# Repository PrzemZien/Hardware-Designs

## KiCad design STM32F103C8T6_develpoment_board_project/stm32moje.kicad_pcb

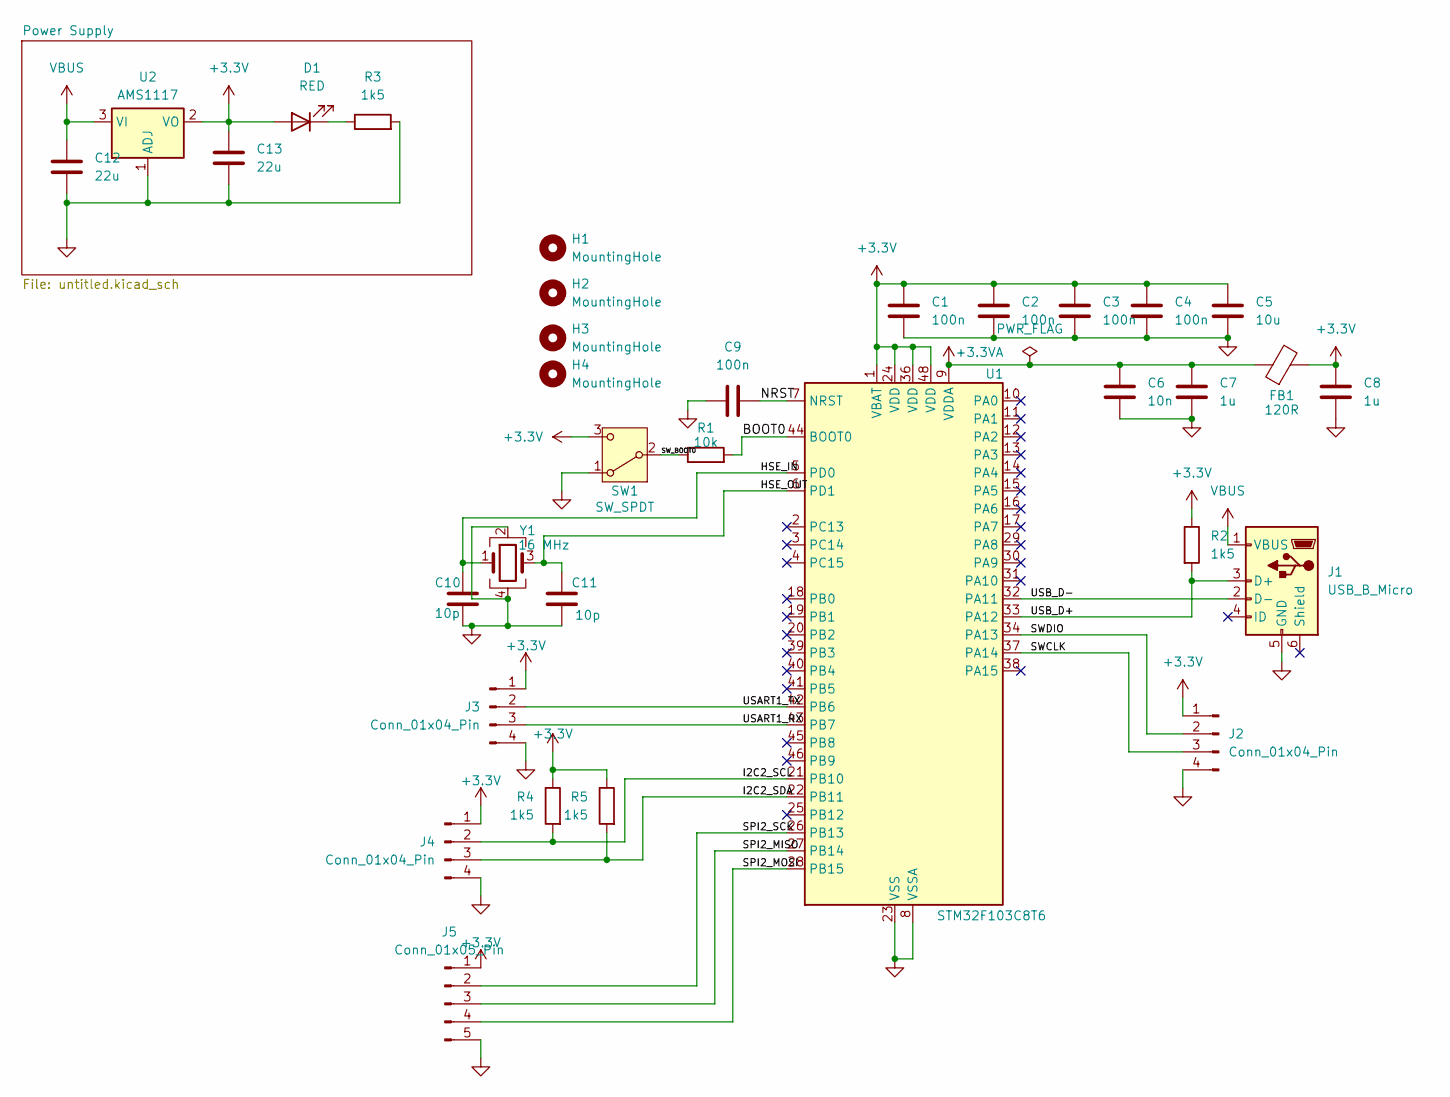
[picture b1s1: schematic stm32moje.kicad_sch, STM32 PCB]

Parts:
C1, C2, C3, C4, C9: 100n; C_0402_1005Metric
C5: 10u; C_0603_1608Metric
C6: 10n; C_0402_1005Metric
C7, C8: 1u; C_0402_1005Metric
C10, C11: 10p; C_0402_1005Metric
C12, C13: 22u; C_0805_2012Metric
D1: RED; LED_0603_1608Metric
FB1: 120R; L_0603_1608Metric
H1, H2, H3, H4: MountingHole; MountingHole_2.2mm_M2
J1: USB_B_Micro; USB_Micro-B_Wuerth_629105150521
J2, J3, J4: Conn_01x04_Pin; PinHeader_1x04_P2.54mm_Vertical
J5: Conn_01x05_Pin; JST_ZE_S05B-ZESK-2D_1x05_P1.50mm_Horizontal
R1: 10k; R_0402_1005Metric
R2, R3, R4, R5: 1k5; R_0402_1005Metric
SW1: SW_SPDT; SW_SPDT_PCM12
U1: STM32F103C8T6; LQFP-48_7x7mm_P0.5mm
U2: AMS1117; SOT-223-3_TabPin2
Y1: 16 MHz; Crystal_SMD_3225-4Pin_3.2x2.5mm

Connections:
+3.3V: C1.1, C2.1, C3.1, C4.1, C5.1, C8.1, C13.1, D1.2 (A), FB1.2, J2.1, J3.1, J4.1, J5.1, R2.1, R4.1, R5.1, SW1.3 (C), U1.1 (VBAT), U1.24 (VDD), U1.36 (VDD), U1.48 (VDD), U2.2 (VO)
+3.3VA: C6.2, C7.1, FB1.1, U1.9 (VDDA)
/BOOT0: R1.2, U1.44 (BOOT0)
/HSE_IN: C10.1, U1.5 (PD0), Y1.1
/HSE_OUT: C11.1, U1.6 (PD1), Y1.3
/I2C2_SCL: J4.2, R4.2, U1.21 (PB10)
/I2C2_SDA: J4.3, R5.2, U1.22 (PB11)
/NRST: C9.2, U1.7 (NRST)
/SPI2_MISO: J5.3, U1.27 (PB14)
/SPI2_MOSI: J5.4, U1.28 (PB15)
/SPI2_SCK: J5.2, U1.26 (PB13)
/SWCLK: J2.3, U1.37 (PA14)
/SWDIO: J2.2, U1.34 (PA13)
/SW_BOOT0: R1.1, SW1.2 (B)
/USART1_RX: J3.3, U1.43 (PB7)
/USART1_TX: J3.2, U1.42 (PB6)
/USB_D+: J1.3 (D+), R2.2, U1.33 (PA12)
/USB_D-: J1.2 (D-), U1.32 (PA11)
GND: C1.2, C2.2, C3.2, C4.2, C5.2, C6.1, C7.2, C8.2, C9.1, C10.2, C11.2, C12.2, C13.2, J1.5 (GND), J2.4, J3.4, J4.4, J5.5, R3.2, SW1.1 (A), U1.8 (VSSA), U1.23 (VSS), U1.35 (VSS), U1.47 (VSS), U2.1 (ADJ), Y1.2, Y1.4
unnamed: D1.1 (K), R3.1
VBUS: C12.1, J1.1 (VBUS), U2.3 (VI)

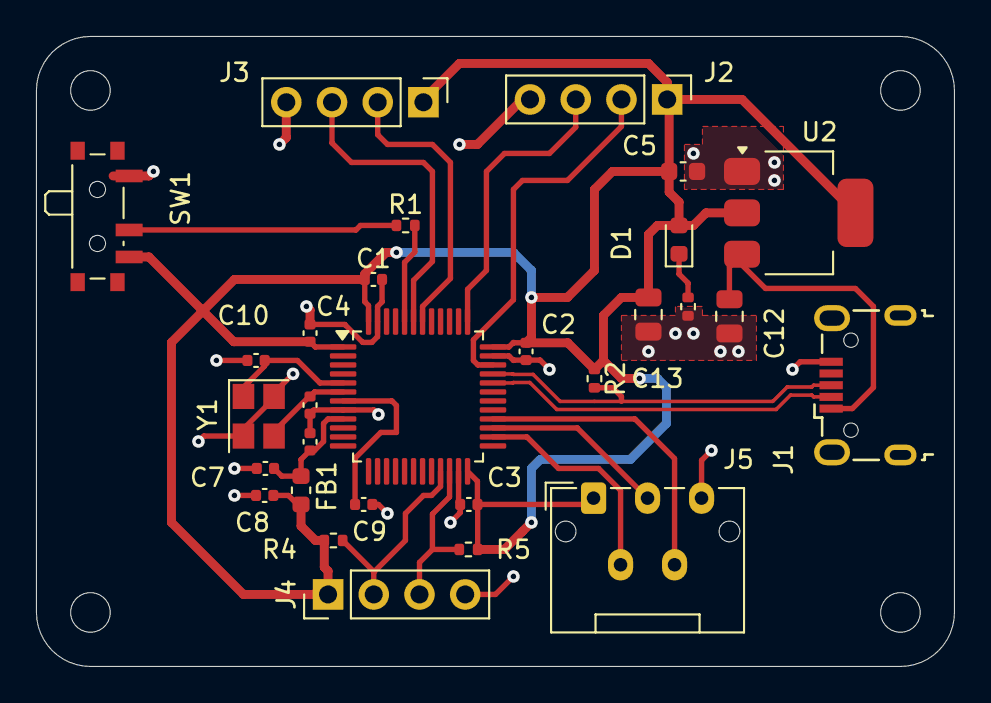
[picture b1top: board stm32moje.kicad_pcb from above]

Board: 2 copper layers, 51.0 x 35.0 mm, 33 parts (0 on the bottom side), 21 nets.

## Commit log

2025-06-29 Create info
2025-06-29 Create trash
